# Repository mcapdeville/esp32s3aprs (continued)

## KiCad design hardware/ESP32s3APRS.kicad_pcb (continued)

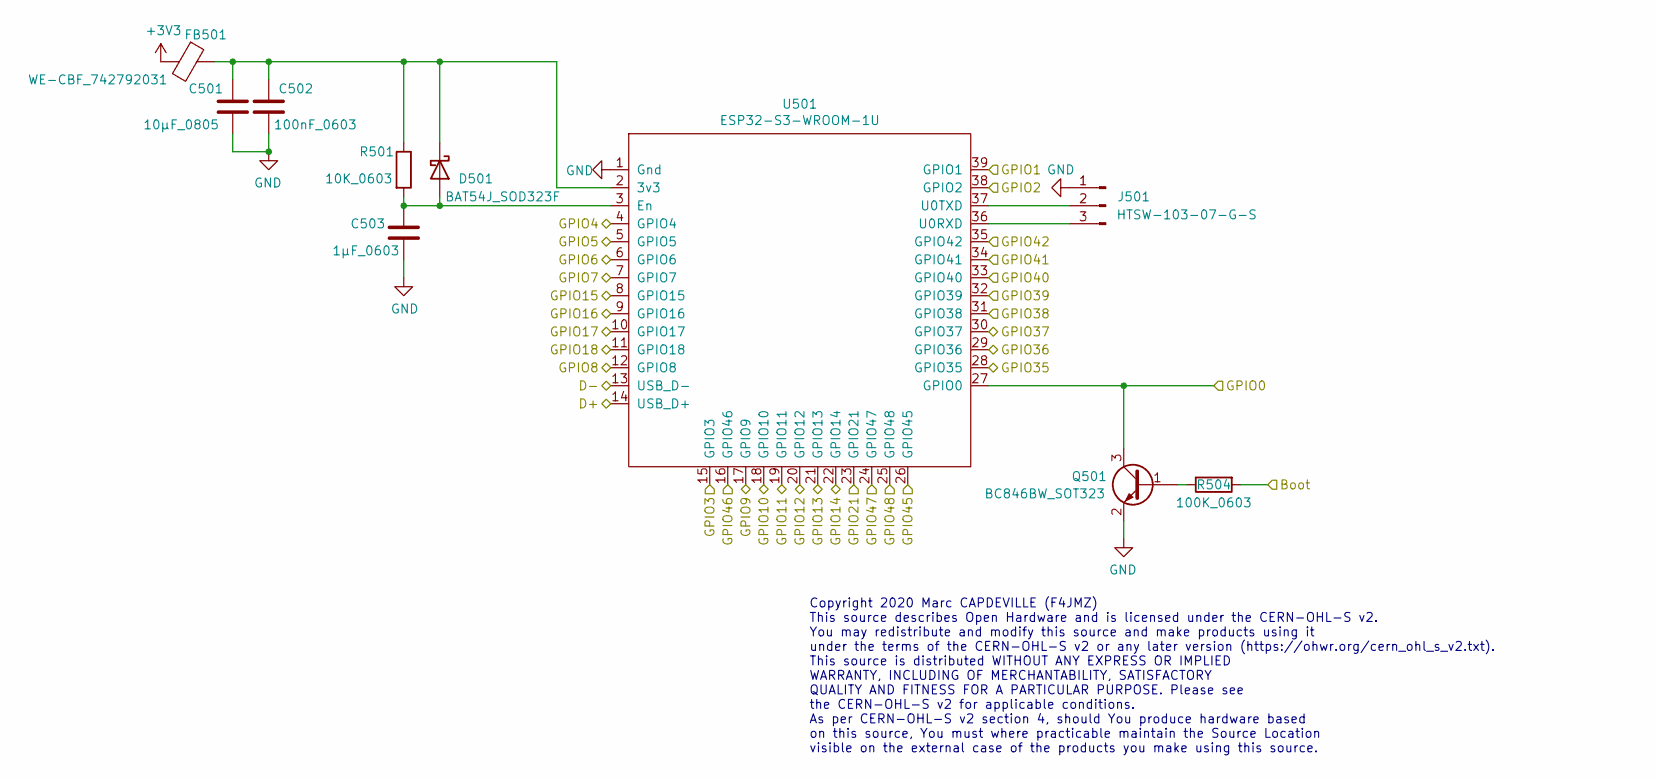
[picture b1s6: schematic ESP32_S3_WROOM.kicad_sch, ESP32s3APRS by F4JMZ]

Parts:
C501: 10µF_0805; C_0805_2012Metric; Mouser 963-TMK212BBJ106MG-T
C502: 100nF_0603; C_0603_1608Metric; Mouser 963-UMK107B7104KAHT
C503: 1µF_0603; C_0603_1608Metric; Mouser 963-UMK107BJ105KA-T
D501: BAT54J_SOD323F; D_SOD-323F; Mouser 771-BAT54J115
FB501: WE-CBF_742792031; L_0805_2012Metric; Mouser 710-742792031
J501: HTSW-103-07-G-S; PinHeader_1x03_P2.54mm_Vertical; Mouser 200-HTSW10307GS
Q501: BC846BW_SOT323; SOT-323_SC-70; Mouser 771-BC846BW-T/R
R501: 10K_0603; R_0603_1608Metric; Mouser 603-RC0603FR-0710KL
R504: 100K_0603; R_0603_1608Metric; Mouser 603-RC0603FR-07100KL
U501: ESP32-S3-WROOM-1U; Mouser 356-ESP32S3WM1UN16R2

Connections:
+3V3: FB501.2; also elsewhere on the board
/AudioIn: U501.12 (GPIO8); also elsewhere on the board
/BAT_ADC: U501.19 (GPIO11); also elsewhere on the board
/BUSY: U501.31 (GPIO38); also elsewhere on the board
/DC: U501.17 (GPIO9); also elsewhere on the board
/ESP32-S3-WROOM/Boot: R504.2; also elsewhere on the board
/ESP32-S3-WROOM/D+: U501.14 (USB_D+); also elsewhere on the board
/ESP32-S3-WROOM/D-: U501.13 (USB_D-); also elsewhere on the board
/ESP32-S3-WROOM/GPIO0: Q501.3 (C), U501.27 (GPIO0); also elsewhere on the board
/ESP32-S3-WROOM/GPIO1: U501.39 (GPIO1); also elsewhere on the board
/ESP32-S3-WROOM/GPIO4: U501.4 (GPIO4); also elsewhere on the board
/ESP32-S3-WROOM/GPIO5: U501.5 (GPIO5); also elsewhere on the board
/ESP32-S3-WROOM/GPIO6: U501.6 (GPIO6); also elsewhere on the board
/ESP32-S3-WROOM/GPIO7: U501.7 (GPIO7); also elsewhere on the board
/ESP32-S3-WROOM/GPIO15: U501.8 (GPIO15); also elsewhere on the board
/ESP32-S3-WROOM/GPIO16: U501.9 (GPIO16); also elsewhere on the board
/ESP32-S3-WROOM/GPIO17: U501.10 (GPIO17); also elsewhere on the board
/ESP32-S3-WROOM/GPIO18: U501.11 (GPIO18); also elsewhere on the board
/ESP32-S3-WROOM/GPIO40: U501.33 (GPIO40); also elsewhere on the board
/FORCE_ON: U501.16 (GPIO46); also elsewhere on the board
/FSPICS0: U501.18 (GPIO10); also elsewhere on the board
/FSPID: U501.28 (GPIO35); also elsewhere on the board
/FSSPICLK: U501.29 (GPIO36); also elsewhere on the board
/GPS1PPS: U501.22 (GPIO14); also elsewhere on the board
/GPSRESET: U501.32 (GPIO39); also elsewhere on the board
/HL: U501.25 (GPIO48); also elsewhere on the board
/PD: U501.26 (GPIO45); also elsewhere on the board
/Ptt: U501.30 (GPIO37); also elsewhere on the board
/SQ: U501.15 (GPIO3); also elsewhere on the board
/SW1: U501.38 (GPIO2); also elsewhere on the board
/SW2: U501.21 (GPIO13); also elsewhere on the board
/SW3: U501.20 (GPIO12); also elsewhere on the board
/U1RX: U501.23 (GPIO21); also elsewhere on the board
/U1TX: U501.24 (GPIO47); also elsewhere on the board
/U2RX: U501.34 (GPIO41); also elsewhere on the board
/U2TX: U501.35 (GPIO42); also elsewhere on the board
Dis: U501.41 (Dis)
GND: C501.2, C502.2, C503.2, J501.1, Q501.2 (E), U501.1 (Gnd), U501.40 (Gnd); also elsewhere on the board
unnamed: C501.1, C502.1, D501.1 (K), FB501.1, R501.1, U501.2 (3v3)
unnamed: C503.1, D501.2 (A), R501.2, U501.3 (En)
unnamed: J501.2, U501.37 (U0TXD)
unnamed: J501.3, U501.36 (U0RXD)
unnamed: Q501.1 (B), R504.1

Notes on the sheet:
Copyright 2020 Marc CAPDEVILLE (F4JMZ) This source describes Open Hardware and is licensed under the CERN-OHL-S v2. You may redistribute and modify this source and make products using it under the terms of the CERN-OHL-S v2 or any later version (https://ohwr.org/cern_ohl_s_v2.txt). This source is d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

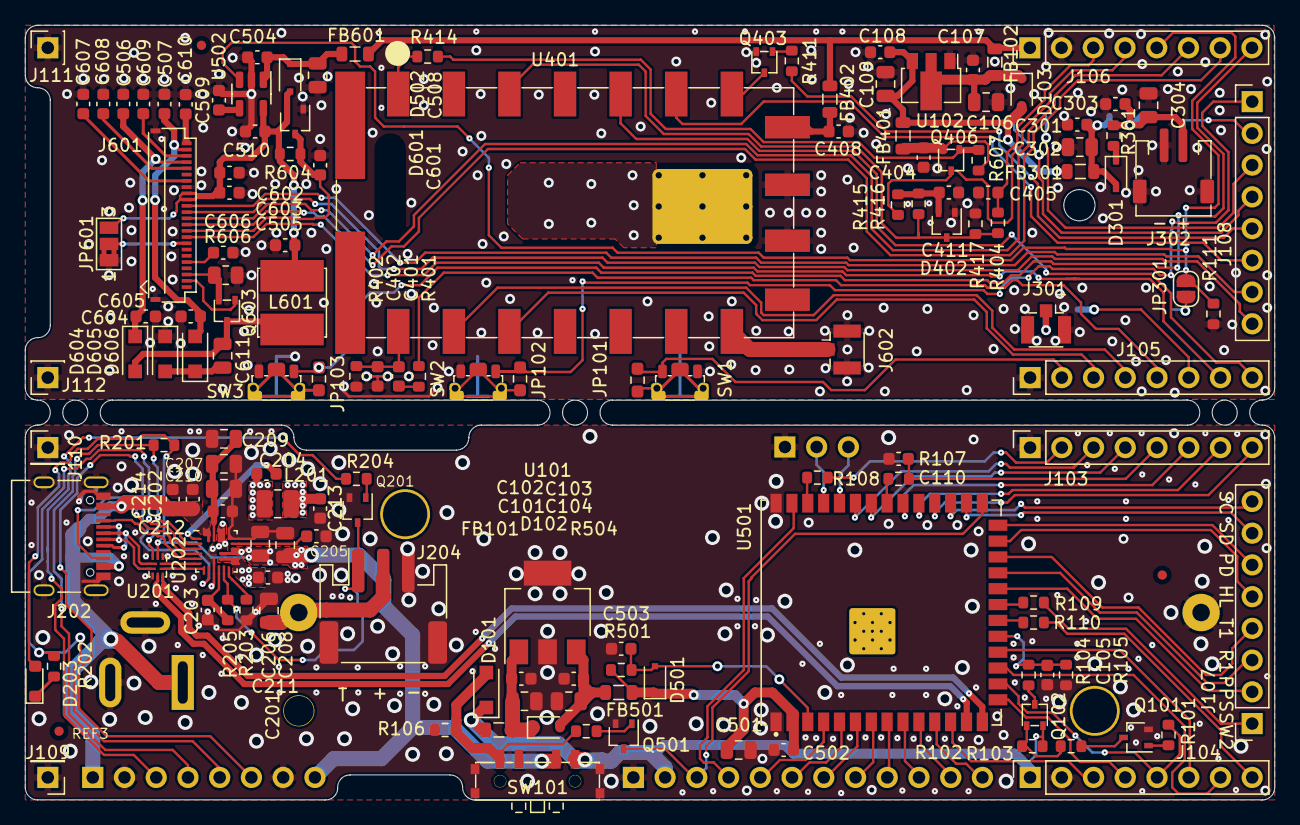
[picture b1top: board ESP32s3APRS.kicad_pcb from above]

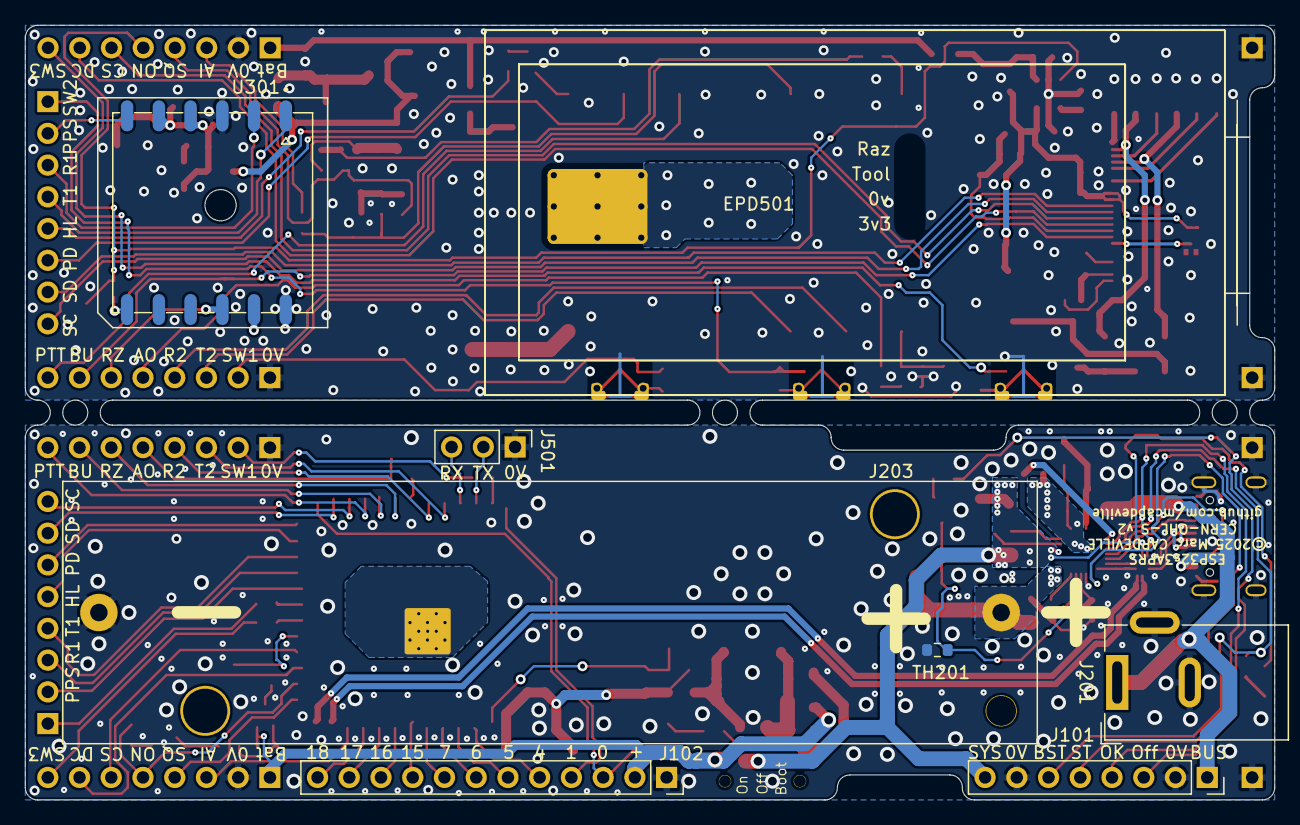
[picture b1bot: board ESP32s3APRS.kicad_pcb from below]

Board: 2 copper layers, 100.0 x 62.0 mm, 156 parts (8 on the bottom side), 131 nets.

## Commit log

2025-04-10 Initial commit
    ESP32s3APRS : v0.0.1
    Esp-idf : v5.5
    TinyUSB : v0.15.0.2
    Lvgl : release/v8.4
    micropython : v1.24-release
2025-04-21 Initial commit
    ESP32s3APRS : v0.0.1
    Esp-idf : v5.4.1
    TinyUSB : v0.15.0.2
    Lvgl : release/v8.4
    micropython : v1.25.0
2025-05-05 hardware : pcb cleanup
2025-05-05 SA8x8 : correct power-up sequence
2025-12-06 AFSK1200 : Using FIR filter
2025-12-18 Hardware cleanup
2025-12-18 Update IDE to v6.0 and somme fix
2025-12-23 Use Tinyusb UAC2 feedback method
    Use Tinyusb audio class device feedback methode for OUT EP with explicit
    feedback.
    Read/Write From/to ep fifo is done in USB_AUDIO_Radio_Cb() in Radio task context.
2025-12-23 Add Dmabuff_Next_Ptr function
    This merge Dmabuff_Get_Ptr() and Dmabuff_Advance_Ptr() in one function
2025-12-23 Use atomic type to count samples
2025-12-23 SA8x8 : use atomic type to count sample
2025-12-23 GPS : fix year representation
2025-12-23 esp-idf : pull update from mcapdeville-v6.0
2025-12-23 main : update logs display use atomic counter
2025-12-23 dependencies and gitmodule update
2025-12-23 spiffs : Add startup script template
2025-12-23 Add 1min test audio file
2025-12-25 Make esp-dsp a submodule
2026-02-15 Add xbm font support for APRS symbols
2026-02-15 Better symbol support.
2026-02-15 Update micropython component
2026-03-21 Minor update
2026-03-26 [APRS] : Altitude on position fixes
2026-03-26 [GPS] Some fixes on Altitude and data validation
2026-03-26 [USB] set CDC buffsize to 256 bytes
2026-03-26 [MAIN] set master and tagged default log level
2026-03-26 reopen stdout as write only
2026-03-26 Set minimal build ON
2026-03-26 Fix missing else
2026-03-26 Revert "reopen stdout as write only"
    This reverts commit 572a9a180fa1e4a47d6aab861280f5e0bbf66c55.
2026-03-26 {MAIN] : fix master log level
2026-03-26 {sdkconfig.default] Add missing options
    Add options to calc precise clock divisor for adc and i2s
    Add master log level option
2026-03-27 [Hardware] : add BOM file as ESP32s3APRS.csv
2026-03-27 [APRS] : Unlink database file before reopen
2026-03-27 [module esp32s3aprs] Add restart() function
2026-03-31 Added picture
2026-03-31 Add Top view immage to readme.md
